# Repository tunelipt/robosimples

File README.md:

# robosimples
Sistema para movimentação do Robô do Túnel de Movimento usando OEM750

A placa do robô do túnel de vento queimou. O sistema usa indexadores OEM-750 para controlar os motores de passo. Esta é uma tentativa simples de controlar os motores de passo. A idéia é, mais para frente fazer um sistema completo que consiga gerar movimentos completos com sensores de fim de curso, etc.

Por enquanto isso aqui é simplesmente um "laboratório" para explorar o problema. Este "laboratório tem as seguintes componentes:

 - Placa eletrônica para 3 eixos controlados por ESP32 Devkit v1 com 30 pinos. Projeto KICAD está na pasta robosimples
 - Programa arduino e C++ que vai na placa localizado na pasta roboesp32
 - Programa + servidor XML-RPC em python
 - Interfaces para outras linguagens de programação.

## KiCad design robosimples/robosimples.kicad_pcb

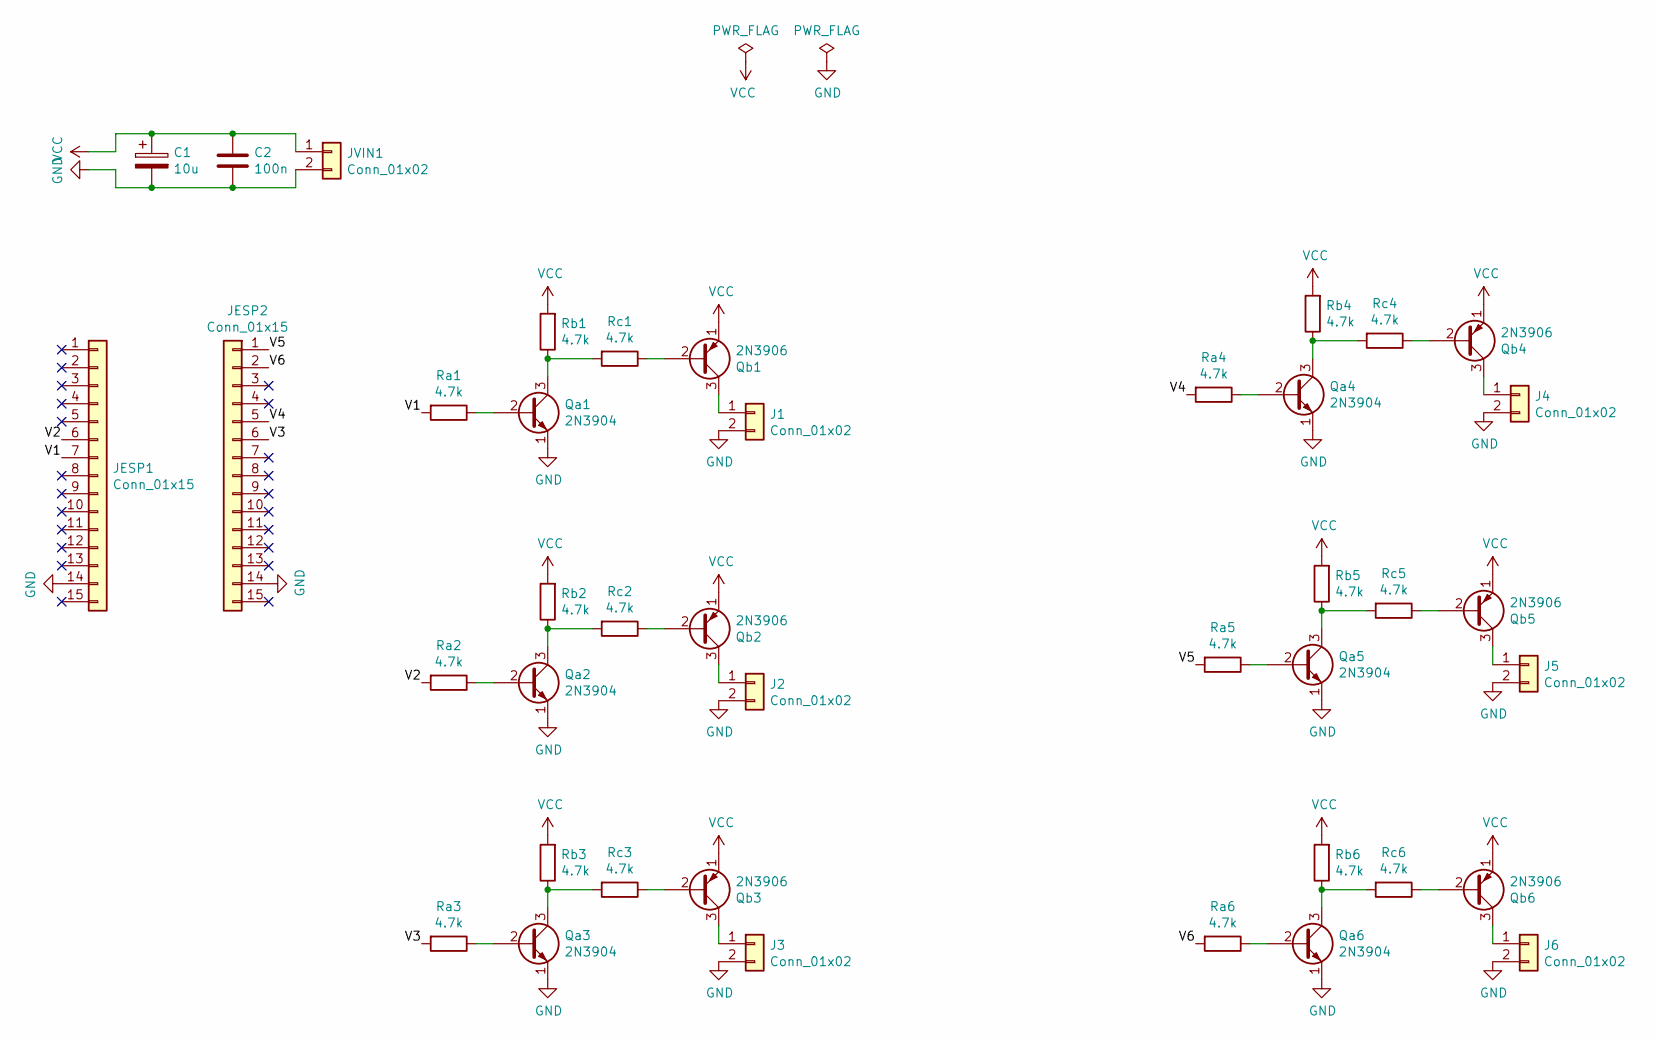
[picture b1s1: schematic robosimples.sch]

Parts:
C1: 10u; CP_Radial_D5.0mm_P2.50mm
C2: 100n; C_Rect_L7.2mm_W3.5mm_P5.00mm_FKS2_FKP2_MKS2_MKP2
J1, J2, J3, J4, J5, J6: Conn_01x02; TerminalBlock_bornier-2_P5.08mm
JESP1, JESP2: Conn_01x15; PinSocket_1x15_P2.54mm_Vertical
JVIN1: Conn_01x02; TerminalBlock_bornier-2_P5.08mm
Qa1, Qa2, Qa3, Qa4, Qa5, Qa6: 2N3904; TO-92_Inline_Wide
Qb1, Qb2, Qb3, Qb4, Qb5, Qb6: 2N3906; TO-92_Inline_Wide
Ra1, Ra2, Ra3, Ra4, Ra5, Ra6: 4.7k; R_Axial_DIN0207_L6.3mm_D2.5mm_P10.16mm_Horizontal
Rb1, Rb2, Rb3, Rb4, Rb5, Rb6: 4.7k; R_Axial_DIN0207_L6.3mm_D2.5mm_P10.16mm_Horizontal
Rc1, Rc2, Rc3, Rc4, Rc5, Rc6: 4.7k; R_Axial_DIN0207_L6.3mm_D2.5mm_P10.16mm_Horizontal

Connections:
/V1: JESP1.7, Ra1.2
/V2: JESP1.6, Ra2.2
/V3: JESP2.6, Ra3.2
/V4: JESP2.5, Ra4.2
/V5: JESP2.1, Ra5.2
/V6: JESP2.2, Ra6.2
GND: C1.2, C2.2, J1.2, J2.2, J3.2, J4.2, J5.2, J6.2, JESP1.14, JESP2.14, JVIN1.2, Qa1.1 (E), Qa2.1 (E), Qa3.1 (E), Qa4.1 (E), Qa5.1 (E), Qa6.1 (E)
unnamed: J1.1, Qb1.3 (C)
unnamed: J2.1, Qb2.3 (C)
unnamed: J3.1, Qb3.3 (C)
unnamed: J4.1, Qb4.3 (C)
unnamed: J5.1, Qb5.3 (C)
unnamed: J6.1, Qb6.3 (C)
unnamed: Qa1.2 (B), Ra1.1
unnamed: Qa1.3 (C), Rb1.1, Rc1.2
unnamed: Qa2.2 (B), Ra2.1
unnamed: Qa2.3 (C), Rb2.1, Rc2.2
unnamed: Qa3.2 (B), Ra3.1
unnamed: Qa3.3 (C), Rb3.1, Rc3.2
unnamed: Qa4.2 (B), Ra4.1
unnamed: Qa4.3 (C), Rb4.1, Rc4.2
unnamed: Qa5.2 (B), Ra5.1
unnamed: Qa5.3 (C), Rb5.1, Rc5.2
unnamed: Qa6.2 (B), Ra6.1
unnamed: Qa6.3 (C), Rb6.1, Rc6.2
unnamed: Qb1.2 (B), Rc1.1
unnamed: Qb2.2 (B), Rc2.1
unnamed: Qb3.2 (B), Rc3.1
unnamed: Qb4.2 (B), Rc4.1
unnamed: Qb5.2 (B), Rc5.1
unnamed: Qb6.2 (B), Rc6.1
VCC: C1.1, C2.1, JVIN1.1, Qb1.1 (E), Qb2.1 (E), Qb3.1 (E), Qb4.1 (E), Qb5.1 (E), Qb6.1 (E), Rb1.2, Rb2.2, Rb3.2, Rb4.2, Rb5.2, Rb6.2

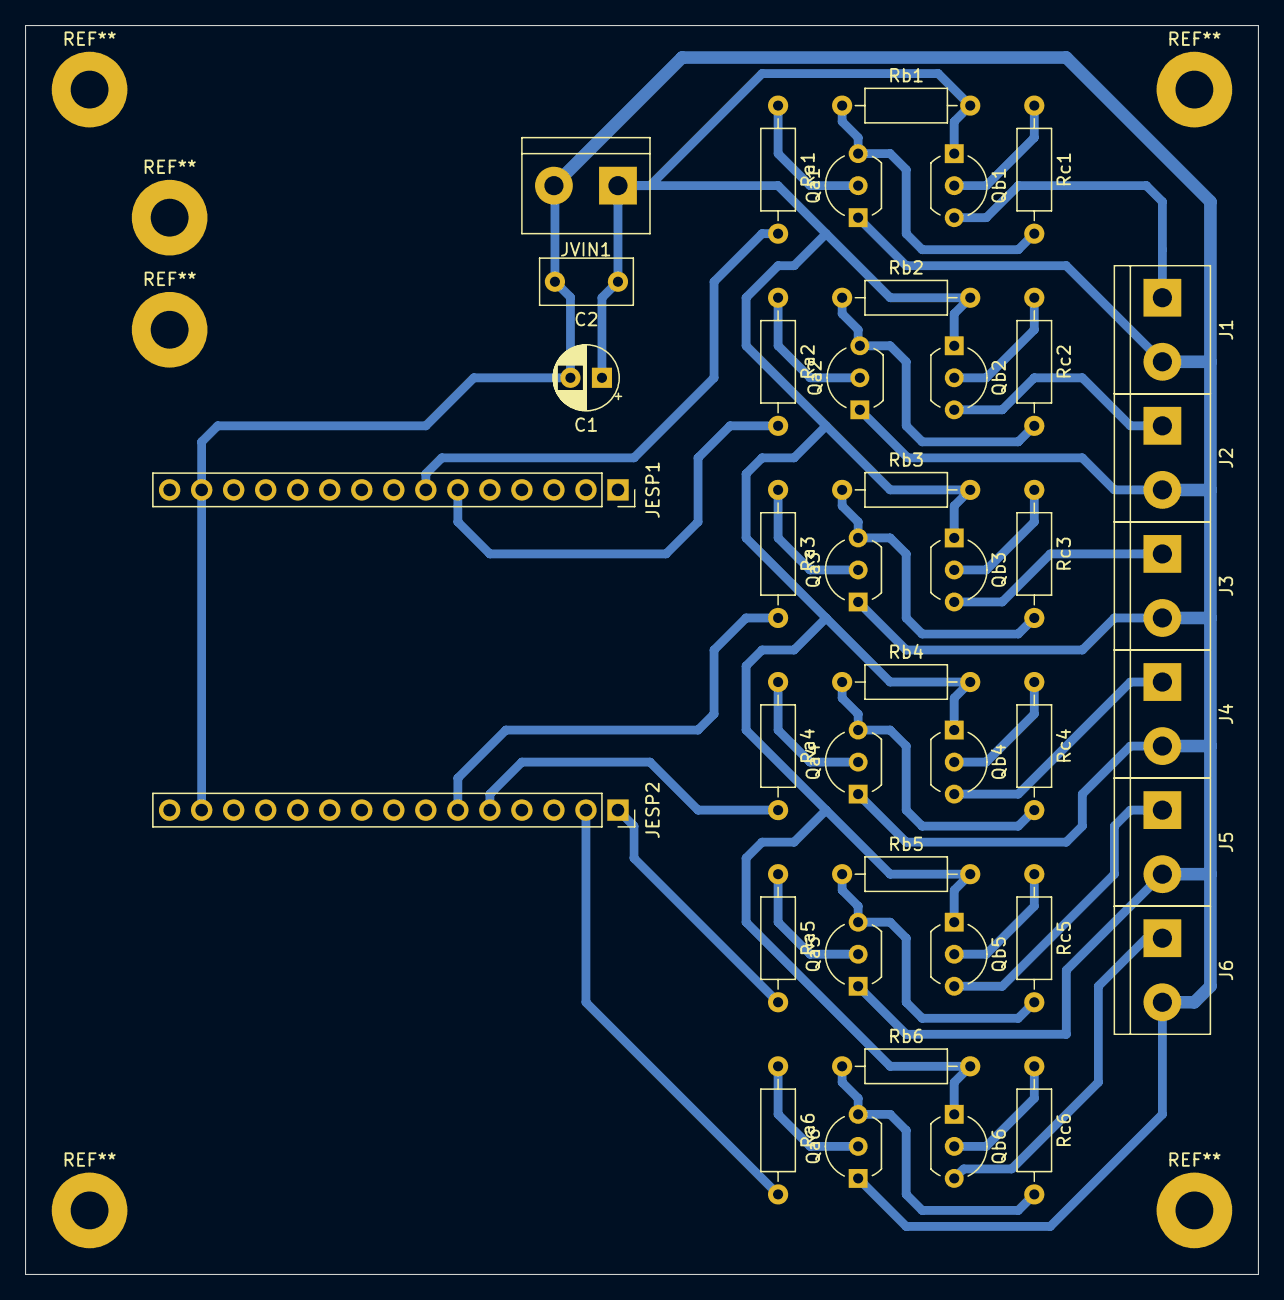
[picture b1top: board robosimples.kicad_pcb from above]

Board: 2 copper layers, 97.8 x 99.1 mm, 41 parts (0 on the bottom side), 32 nets.

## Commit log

2021-04-16 Commit inicial da placa do robo simples
    Esta é uma placa simples só para ter a funcionalidade básica e permitir estudar o problema.
2021-04-16 Trabalhando no README.md
2021-08-02 Acertando os valores para o eixo x
2021-08-02 Interface Python inicial
    Apenas o jeitão por enquanto. Mas funcionando.
2021-08-10 Implemented acceleration
    Now you can specify an acceleration ramp.
2021-08-27 Três eixos podem ser usados!
    Ainfa mexendo na parte do esp32. Preciso ainda implementar
    a interface Python.
2021-08-27 The esp board can handle 3 axes and a better protocol was implemented
    The functionality is very simple and should be improved upon. But it
    satisfies our minimal needs. Still need to implement the python interface.
2021-08-27 Created python interface
    The interface appears to be working. I still need to test it on
    the actual cartesian robot.
2021-08-27 Corrected small bugs
    The code appears to be working!
